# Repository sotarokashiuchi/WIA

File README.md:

# WIA (Who Is Absent)
WIAは、学生証を用いて出席確認を自動化し、手間やミスを削減するための出席管理システムです。パソコンやスマートフォンなど、すべての端末から操作可能で、オフラインで完結するのが特徴です。

## 特徴
- 学生証を利用した出席確認
- 高速かつ正確な一括出席管理
- オフラインで完結（電源さえあれば動作可能）
- Webブラウザから操作可能（端末を問わず）

## 主な機能
- 学生証の登録
- 出席簿の作成と管理
- 出席確認
- 手動入力対応
- CSV形式での出力
- 時刻同期機能
- デーモン化による自動起動
- シャットダウン機能

## システム構成

## デモンストレーション
### ユーザ登録

### 出席簿作成

### 出席簿

## Setup
```shell
# copy systemd file
cd ACPj/systemd/systemd
sudo cp HttpEcho.service NFCTouch.service /lib/systemd/system/

# start demon
sudo systemctl daemon-reload
sudo systemctl enable NFCTouch.service
sudo systemctl enable HttpEcho.service

# setting shutdown pin
sudo vi /boot/config.txt
# add to /boot/config.txt
dtoverlay=gpio-shutdown,gpio_pin=4,debounce=2000

# reboot
sudo reboot
```

## Remote Desktop
1. ラズベリーパイとパソコンをEthernetケーブルで接続する
2. パソコンの有線ケーブルに静的IPアドレス`169.254.26.5`, マスクを`255.255.255.0`を割り当てる
3. SSH接続(Tera Term 5を使うと良い)または、RDP接続(windowsならmstscを LinuxならRemminaを使うと良い)を行う
   - ラズベリーパイのIPアドレス`169.254.26.30`
   - Username denki
   - Password password

## 部品
| 名称                  | 数量   |
| --------------------- | ------ |
| Raspberry Pi 2B       | 1      |
| M2*5~7                | 8      |
| M2スペーサ            | 4      |
| ピンヘッダ20*2        | 1      |
| RFID-RC522            | 1      |
| M3*9~12               | 4      |
| I2C transport LCD     | 1      |
| M3*12~15              | 4      |
| M3ボルト              | 8      |
| RTC                   | 1      |
| M2*8~11               | 3      |
| M2ボルト              | 3      |
| RotaryEncoder_Switch  | 1      |
| 抵抗 130Ω             | 3      |
| スイッチ              | 5 or 6 |
| LED(RED, BLUE, GREEN) | 3      |
| ブザー                | 1      |

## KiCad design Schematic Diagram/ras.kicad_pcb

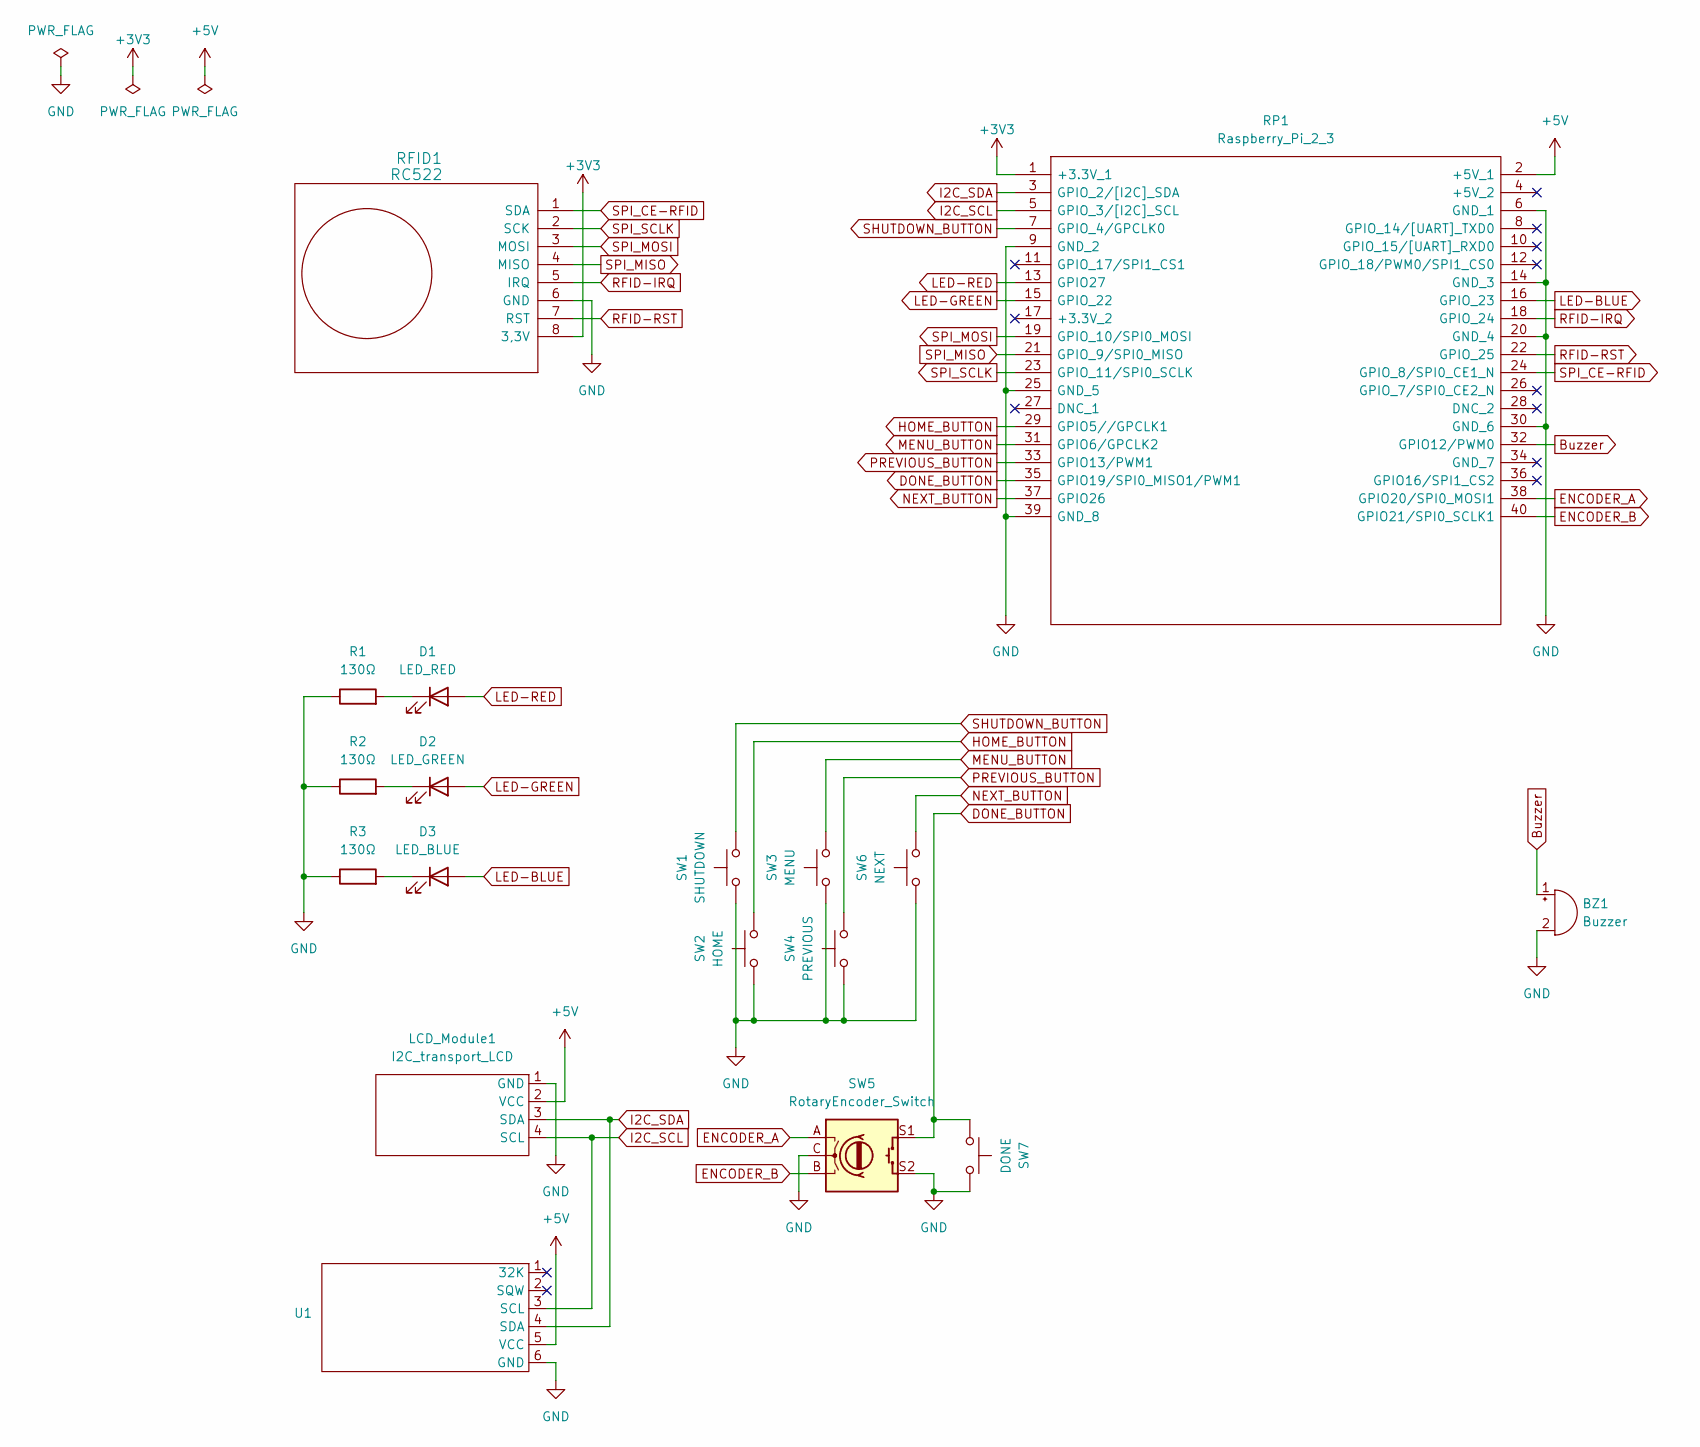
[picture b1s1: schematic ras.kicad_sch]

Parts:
BZ1: Buzzer; Buzzer_12x9.5RM7.6
D1: LED_RED; LED_D5.0mm
D2: LED_GREEN; LED_D5.0mm
D3: LED_BLUE; LED_D5.0mm
LCD_Module1: I2C_transport_LCD; WC1602A
R1, R2, R3: 130Ω; R_Axial_DIN0207_L6.3mm_D2.5mm_P7.62mm_Horizontal
RFID1: RC522; RFID-RC522
RP1: Raspberry_Pi_2_3; raspberrypi3; Manufacturer_Part_Number Raspberry Pi 2 or 3
SW1: SHUTDOWN; SW_PUSH_6mm
SW2: HOME; SW_PUSH_6mm
SW3: MENU; SW_PUSH_6mm
SW4: PREVIOUS; SW_PUSH_6mm
SW5: RotaryEncoder_Switch; RotaryEncoder_Alps_EC12E-Switch_Vertical_H20mm
SW6: NEXT; SW_PUSH_6mm
SW7: DONE; SW_PUSH_6mm
U1: DS3231M

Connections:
+3V3: RFID1.8 (3,3V), RP1.1 (+3.3V_1)
+5V: LCD_Module1.2 (VCC), RP1.2 (+5V_1), U1.5 (VCC)
Buzzer: BZ1.1 (-), RP1.32 (GPIO12/PWM0)
DONE_BUTTON: RP1.35 (GPIO19/SPI0_MISO1/PWM1), SW5.S1, SW7.1
ENCODER_A: RP1.38 (GPIO20/SPI0_MOSI1), SW5.A
ENCODER_B: RP1.40 (GPIO21/SPI0_SCLK1), SW5.B
GND: BZ1.2 (+), LCD_Module1.1 (GND), R1.1, R2.1, R3.1, RFID1.6 (GND), RP1.6 (GND_1), RP1.9 (GND_2), RP1.14 (GND_3), RP1.20 (GND_4), RP1.25 (GND_5), RP1.30 (GND_6), RP1.39 (GND_8), SW1.1, SW2.1, SW3.1, SW4.1, SW5.C, SW5.S2, SW6.1, SW7.2, U1.6 (GND)
HOME_BUTTON: RP1.29 (GPIO5//GPCLK1), SW2.2
I2C_SCL: LCD_Module1.4 (SCL), RP1.5 (GPIO_3/[I2C]_SCL), U1.3 (SCL)
I2C_SDA: LCD_Module1.3 (SDA), RP1.3 (GPIO_2/[I2C]_SDA), U1.4 (SDA)
LED-BLUE: D3.2 (A), RP1.16 (GPIO_23)
LED-GREEN: D2.2 (A), RP1.15 (GPIO_22)
LED-RED: D1.2 (A), RP1.13 (GPIO27)
MENU_BUTTON: RP1.31 (GPIO6/GPCLK2), SW3.2
NEXT_BUTTON: RP1.37 (GPIO26), SW6.2
unnamed: D1.1 (K), R1.2
unnamed: D2.1 (K), R2.2
unnamed: D3.1 (K), R3.2
PREVIOUS_BUTTON: RP1.33 (GPIO13/PWM1), SW4.2
RFID-IRQ: RFID1.5 (IRQ), RP1.18 (GPIO_24)
RFID-RST: RFID1.7 (RST), RP1.22 (GPIO_25)
SHUTDOWN_BUTTON: RP1.7 (GPIO_4/GPCLK0), SW1.2
SPI_CE-RFID: RFID1.1 (SDA), RP1.24 (GPIO_8/SPI0_CE1_N)
SPI_MISO: RFID1.4 (MISO), RP1.21 (GPIO_9/SPI0_MISO)
SPI_MOSI: RFID1.3 (MOSI), RP1.19 (GPIO_10/SPI0_MOSI)
SPI_SCLK: RFID1.2 (SCK), RP1.23 (GPIO_11/SPI0_SCLK)

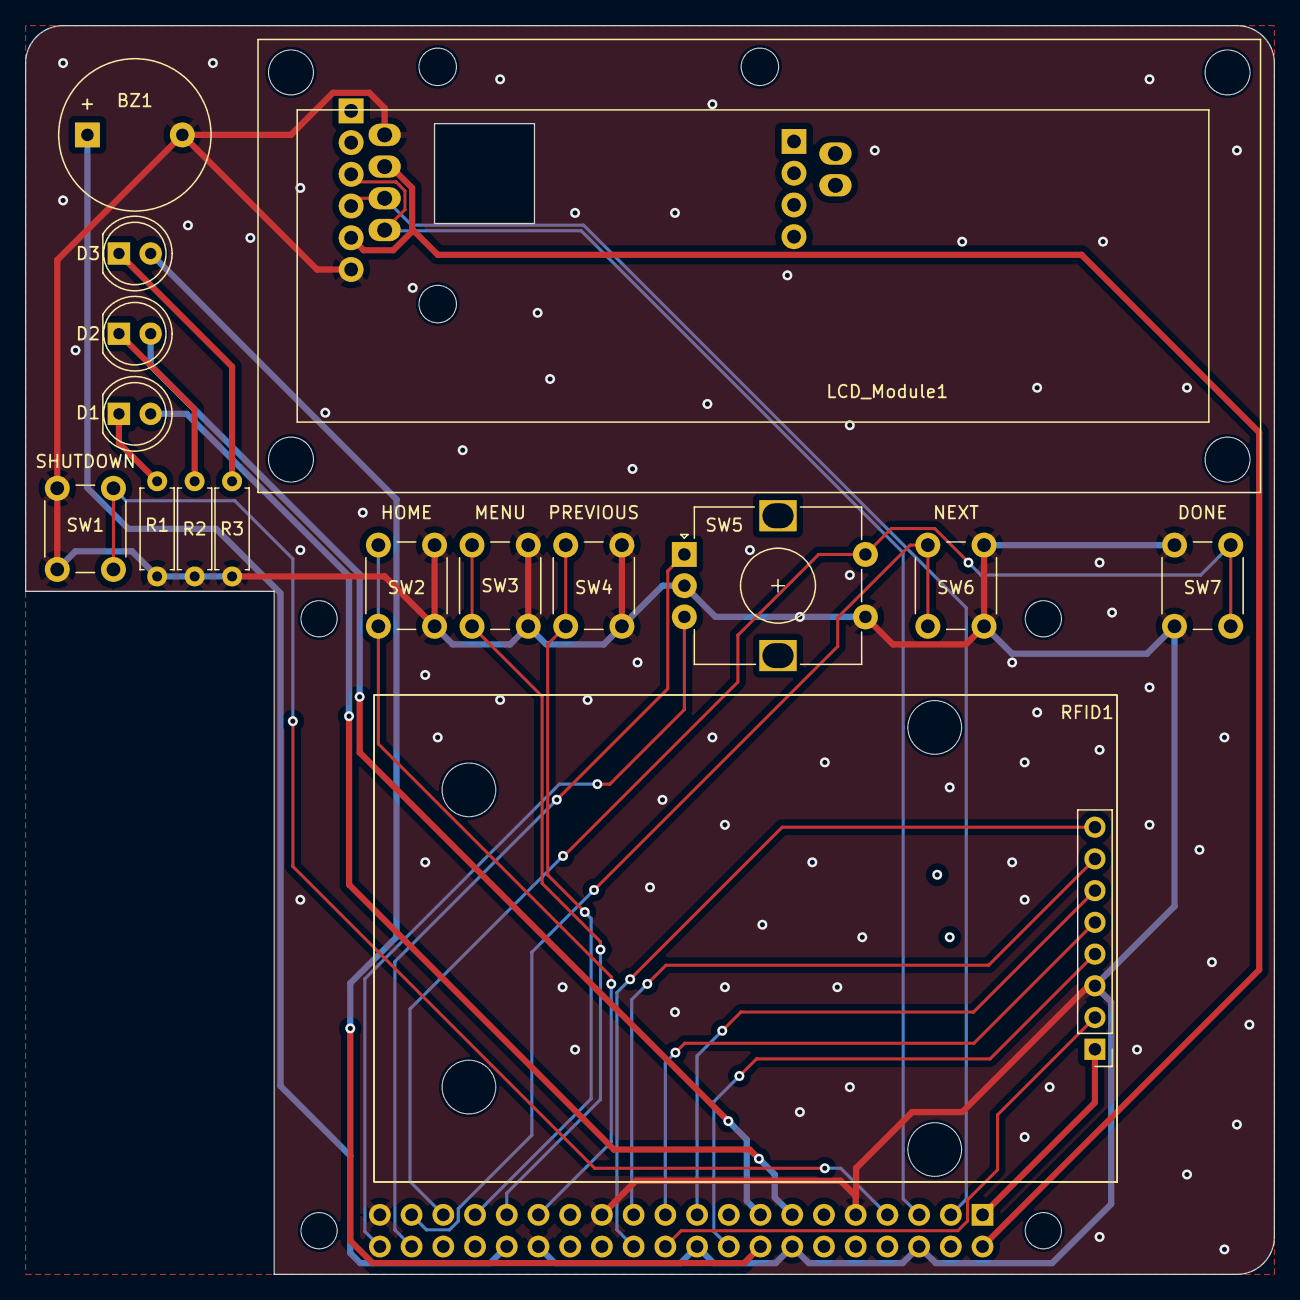
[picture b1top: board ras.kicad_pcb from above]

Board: 2 copper layers, 100.0 x 100.0 mm, 18 parts (1 on the bottom side), 26 nets.

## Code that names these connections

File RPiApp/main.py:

import RPi.GPIO as GPIO
import requests
import time
import i2clcda as lcd
from pirc522 import RFID
import tone
import encoder as ENCODER
import subprocess

HIGH = 1
LOW = 0
LED_GREEN = 22
LED_RED = 27
LED_BLUE = 23
BUZZER = 12
ROTARY_ENCODER_A = 20
ROTARY_ENCODER_B = 21
HOME_BUTTON = 5
MENU_BUTTON = 6
PREVIOUS_BUTTON = 13
DONE_BUTTON = 19
NEXT_BUTTON = 26

SW_ON = 0
SW_OFF = 1

rdr = RFID(pin_rst=25, pin_irq=24, pin_mode=GPIO.BCM)
buzzerPWM = tone.Tone(BUZZER)
encoder = ENCODER.Encoder(ROTARY_ENCODER_A, ROTARY_ENCODER_B)

def initialize():
    GPIO.setmode(GPIO.BCM)
    GPIO.setwarnings(False)
    GPIO.setup(LED_RED, GPIO.OUT, initial=GPIO.LOW)
    GPIO.setup(LED_GREEN, GPIO.OUT, initial=GPIO.LOW)
    GPIO.setup(LED_BLUE, GPIO.OUT, initial=GPIO.LOW)
    GPIO.setup(ROTARY_ENCODER_A, GPIO.IN, pull_up_down=GPIO.PUD_UP)
    GPIO.setup(ROTARY_ENCODER_B, GPIO.IN, pull_up_down=GPIO.PUD_UP)
    GPIO.setup(MENU_BUTTON, GPIO.IN, pull_up_down=GPIO.PUD_UP)
    GPIO.setup(NEXT_BUTTON, GPIO.IN, pull_up_down=GPIO.PUD_UP)
    GPIO.setup(PREVIOUS_BUTTON, GPIO.IN, pull_up_down=GPIO.PUD_UP)
    GPIO.setup(DONE_BUTTON, GPIO.IN, pull_up_down=GPIO.PUD_UP)
    GPIO.setup(HOME_BUTTON, GPIO.IN, pull_up_down=GPIO.PUD_UP)

    lcd.lcd_init()
    lcd.lcd_string("> Completed", lcd.LCD_LINE_1)
    lcd.lcd_string("> Initialize!!", lcd.LCD_LINE_2)


def finalize():
    GPIO.cleanup()
    rdr.cleanup()
    lcd.lcd_byte(0x01, lcd.LCD_CMD)
    buzzerPWM.destroy()
    return

def requestNFCToch(serialNumber):
    response = requests.post(
            "http://localhost:1234/nfc/touch",
            headers={"Content-Type": "application/x-www-form-urlencoded"},
            data={"serialNumber": serialNumber}
    )

    return response.json()["name"]

def readTagUID():
    rdr.wait_for_tag(1)
    (error, tag_type) = rdr.request()
    if not error:
        (error, uid) = rdr.anticoll()
        if not error:
            return str(uid)

def wait_sw_off(SW):
    while GPIO.input(SW)==SW_ON:
        pass
    return

def menu():
    lcd_menu = [
                    [
                        ">Attendance",
                        " Time  WiFi"
                    ],[
                        " Attendance",
                        ">Time  WiFi"
                    ],[
                        " Attendance",
                        " Time >WiFi"
                    ]
                ]
    lcd_menu_index=0

    while GPIO.input(DONE_BUTTON)!=SW_ON:
        lcd.lcd_string(lcd_menu[lcd_menu_index][0], lcd.LCD_LINE_1)
        lcd.lcd_string(lcd_menu[lcd_menu_index][1], lcd.LCD_LINE_2)
        lcd.lcd_display_on()
        if GPIO.input(HOME_BUTTON)==SW_ON:
            wait_sw_off(HOME_BUTTON)
            return
        if GPIO.input(NEXT_BUTTON)==SW_ON:
            lcd_menu_index=lcd_menu_index+1
            if lcd_menu_index >= 3:
                lcd_menu_index=2
            wait_sw_off(NEXT_BUTTON)
        if GPIO.input(PREVIOUS_BUTTON)==SW_ON:
            lcd_menu_index=lcd_menu_index-1
            if lcd_menu_index < 0:
                lcd_menu_index=0
            wait_sw_off(PREVIOUS_BUTTON)
    
    wait_sw_off(DONE_BUTTON)

    if lcd_menu_index==0:
        set_attendance()
    elif lcd_menu_index==1:
        set_time()
    elif lcd_menu_index==2:
        get_wifi()

def set_attendance():
    pass

def set_time():
    lcd_time = [
              # "YYYY/MM/DD HH:MM",
                "   ^            ",
                "      ^         ",
                "         ^      ",
                "            ^   ",
                "               ^",
            ]
    lcd_time_index=0
    lcd_count=250

    now_time = subprocess.check_output(["sudo", "hwclock", "-r"])
    now_time = now_time.decode('utf-8')
    setting_time = [
            int(now_time[0:4]),
            int(now_time[5:7]),
            int(now_time[8:10]),
            int(now_time[11:13]),
            int(now_time[14:16])
        ]


    while GPIO.input(DONE_BUTTON)!=0:
        if lcd_count==250:
            lcd.lcd_string(str(setting_time[0]).zfill(4)+"/"+str(setting_time[1]             ).zfill(2)+"/"+str(setting_time[2]).zfill(2)+" "+str(setting_time[3]).zfill(2)+"             :"+str(setting_time[4]).zfill(2), lcd.LCD_LINE_1)
            lcd.lcd_string(lcd_time[lcd_time_index], lcd.LCD_LINE_2)
            # lcd.lcd_display_on()
            lcd_count=0
        else:
            lcd_count=lcd_count+1

        if GPIO.input(HOME_BUTTON)==0:
            wait_sw_off(HOME_BUTTON)
            return
        if GPIO.input(NEXT_BUTTON)==0:
            lcd_time_index=lcd_time_index+1
            if lcd_time_index >= 5:
                lcd_time_index=4
            wait_sw_off(NEXT_BUTTON)
        if GPIO.input(PREVIOUS_BUTTON)==0:
            lcd_time_index=lcd_time_index-1
            if lcd_time_index < 0:
                lcd_time_index=0
            wait_sw_off(PREVIOUS_BUTTON)

        encoder.set(setting_time[lcd_time_index])
        data = encoder.read()
        if lcd_time_index==1:
            if data>12:
                data=1
            if data<=0:
                data=12
        elif lcd_time_index==2:
            if data>31:
                data=1
            if data<=0:
                data=31
        elif lcd_time_index==3:
            if data>23:
                data=0
            if data<0:
                data=23
        elif lcd_time_index==4:
            if data>59:
                data=0
            if data<0:
                data=59
        setting_time[lcd_time_index] = data

    subprocess.call(["sudo", "date", "-s", str(setting_time[0]).zfill(4)+"/"+str             (setting_time[1]).zfill(2)+"/"+str(setting_time[2]).zfill(2)+" "+str(setting_tim             e[3]).zfill(2)+":"+str(setting_time[4]).zfill(2)])
    subprocess.call(["sudo", "hwclock", "-w"])

def get_wifi():
    pass

def main():
    serialNumber = ""
    name = ""
    oldSerialNumber = ""
    oldTimeStanp = 0
    while True:
        if GPIO.input(MENU_BUTTON)==SW_ON:
            menu()

        # NFC読み取り処理
        oldSerialNumber = serialNumber
        oldTimeStanp = time.time()
        serialNumber = readTagUID()
        if oldSerialNumber == serialNumber and time.time()-oldTimeStanp < 0.01:
            time.sleep(0.1)
            continue
        
        name = requestNFCToch(serialNumber)
        lcd.lcd_display_off()
        if name == "":
            # 名前の未登録
            buzzerPWM.beep(440)
            lcd.lcd_string("Warning", lcd.LCD_LINE_1)
            lcd.lcd_string("Not Registered", lcd.LCD_LINE_2)
            lcd.lcd_display_on()
            GPIO.output(BUZZER, HIGH)
            GPIO.output(LED_RED, HIGH)
            time.sleep(0.05)
            buzzerPWM.none()
        else:
            # 正常処理
            requestNFCToch(serialNumber)
            buzzerPWM.beep(2000)
            lcd.lcd_string("Completed!", lcd.LCD_LINE_1)
            lcd.lcd_string(name, lcd.LCD_LINE_2)
            lcd.lcd_display_on()
            GPIO.output(BUZZER, HIGH)
            GPIO.output(LED_BLUE, HIGH)
            time.sleep(0.05)
            buzzerPWM.none()
        
        time.sleep(0.75)
        GPIO.output(LED_GREEN, LOW)
        GPIO.output(LED_BLUE, LOW)
        GPIO.output(LED_RED, LOW)
        lcd.lcd_init()
    return

if __name__ == '__main__':
    try:
        initialize()
        main()
    except KeyboardInterrupt:
        pass
    finally:
        finalize()

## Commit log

2024-04-26 git init
2024-04-27 add lib of raspberrypi
2024-04-27 add lib of RC522
2024-04-27 .gitignore
2024-04-27 set RC522
2024-04-27 I2C transport LCD
2024-04-27 put RC522
2024-04-27 put LED
2024-04-27 refactaring
2024-04-27 put buzzer
2024-04-29 golang echo freamwark
2024-04-29 add templete
2024-04-29 createDB()
2024-04-29 fmted
2024-04-29 loadAttendanceDB()
2024-04-30 select()
2024-04-30 attendanceNewGET()
2024-04-30 attendanceNewPOST()
2024-04-30 nfcTouchPOST()
2024-05-01 collect function
2024-05-02 userEditGET()
2024-05-02 userEditPOST()
2024-05-02 attendanceDownloadGET()
2024-05-02 Download CSV file
2024-05-02 add bootstrap
2024-05-02 allow bootstrap
2024-05-14 抵抗値変更
2024-05-15 RPiApp
2024-05-15 requestNFCTouch
2024-05-15 buzzer
2024-05-15 add module LCD
2024-05-20 LED and BUZZER
2024-05-20 add comment of I2C
    comment
2024-05-20 try-expect stem
2024-05-20 LCD カタカナ
2024-05-20 read NFC
2024-05-27 LCD カタカナ動作確認
2024-05-27 RC522
2024-05-27 read UID of Tag
2024-05-29 create tone class
2024-05-29 use tone class
2024-05-29 support smartphone close #2
2024-05-29 change title
2024-07-02 jst data close #3
2024-07-02 up speed of LCD display and clean string of LCD
2024-07-02 change status of creating attendance
2024-07-02 readSerialNumber
2024-07-02 add README.md
2024-07-02 change struct of Attendance, add status
2024-07-02 attedanceStatusGet()
2024-07-02 db init
2024-07-02 add shutdown switch close #6
2024-07-02 add reset and sample
2024-07-02 divide func of nfcTouch
2024-07-02 add setting time close #4
2024-07-02 fix update timestanp
2024-07-02 manual attendance close #5
2024-07-02 change tone times
2024-07-02 change UI
2024-07-02 時間外の出席簿を有効にできないように制限
2024-07-02 add systemd
2024-07-02 fix bug of lcd.string()
2024-07-02 tone
2024-07-02 NFCカードが一度話された場合のみ値を更新
2024-07-02 clear brawser cash
2024-07-02 update AttendanceDB
2024-07-02 update Schematic Diagram
2025-04-01 create automatically attendance
2025-04-02 reneme file
2025-04-08 update READM: add Remote desktop
2025-04-17 update ras and vertify RFID and LED
2025-04-17 verify I2C
2025-04-17 vertify encoder and button
2025-04-20 add menu
2025-04-20 set time
2025-04-21 check ERC
2025-05-02 create fp-lib and fp-table
2025-05-02 display parts
2025-05-02 fix fp
2025-05-02 wiring
2025-05-03 create log
2025-05-03 add logo
2025-05-09 pass DRC checks
2025-05-16 fix PCB design (closed #7)
2025-05-16 add parts list to README
2025-05-17 Update README with project description and features; add system configuration diagram
2025-05-17 Enhance README with demonstration section and add new images for user registration, attendance creation, and system configuration
2025-08-28 Update README to include additional hardware images for enhanced visual representation
